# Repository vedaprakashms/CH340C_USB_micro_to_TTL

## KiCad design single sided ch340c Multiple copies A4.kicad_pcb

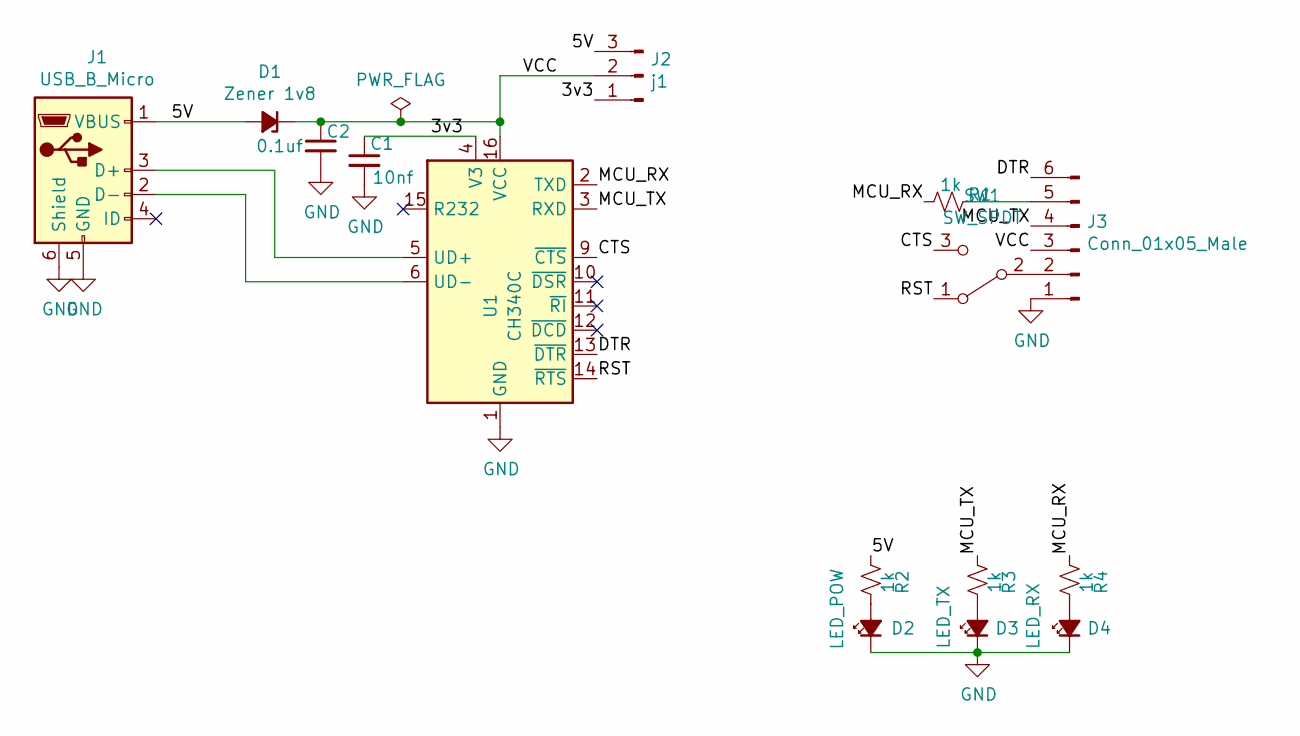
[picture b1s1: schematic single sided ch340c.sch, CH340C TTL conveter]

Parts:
C1: 10nf; C_0805_2012Metric_Pad1.15x1.40mm_HandSolder
C2: 0.1uf; C_0805_2012Metric_Pad1.15x1.40mm_HandSolder
D1: Zener 1v8; D_0805_2012Metric_Pad1.15x1.40mm_HandSolder
D2: LED_POW; LED_0805_2012Metric_Pad1.15x1.40mm_HandSolder
D3: LED_TX; LED_0805_2012Metric_Pad1.15x1.40mm_HandSolder
D4: LED_RX; LED_0805_2012Metric_Pad1.15x1.40mm_HandSolder
J1: USB_B_Micro; USB_Micro-B_Molex_47346-0001
J2: j1; PinHeader_1x03_P2.54mm_Vertical
J3: Conn_01x05_Male; PinHeader_1x06_P2.54mm_Vertical
R1, R2, R3, R4: 1k; R_0805_2012Metric_Pad1.15x1.40mm_HandSolder
SW1: SW_SPDT; PinHeader_1x03_P2.54mm_Vertical
U1: CH340C; SOIC-16_3.9x9.9mm_P1.27mm

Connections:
/3v3: C1.1, J2.1, U1.4 (V3)
/5V: D1.2 (A), J1.1 (VBUS), J2.3, R2.1
/CTS: SW1.3 (C), U1.9 (~CTS)
/DTR: J3.6, U1.13 (~DTR)
/MCU_RX: R1.1, R4.1, U1.2 (TXD)
/MCU_TX: J3.4, R3.1, U1.3 (RXD)
/RST: SW1.1 (A), U1.14 (~RTS)
/VCC: C2.1, D1.1 (K), J2.2, J3.3, U1.16 (VCC)
GND: C1.2, C2.2, D2.1 (K), D3.1 (K), D4.1 (K), J1.5 (GND), J1.6 (Shield), J3.1, U1.1 (GND)
unnamed: D2.2 (A), R2.2
unnamed: D3.2 (A), R3.2
unnamed: D4.2 (A), R4.2
unnamed: J1.2 (D-), U1.6 (UD-)
unnamed: J1.3 (D+), U1.5 (UD+)
unnamed: J3.2, SW1.2 (B)
unnamed: J3.5, R1.2

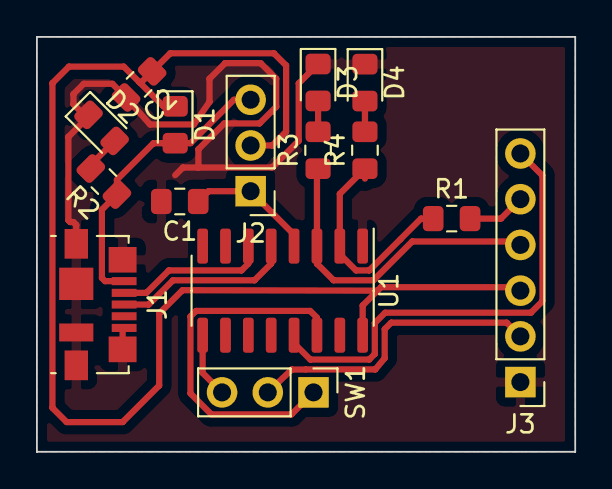
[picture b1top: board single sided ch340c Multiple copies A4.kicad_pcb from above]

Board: 2 copper layers, 29.9 x 23.1 mm, 15 parts (0 on the bottom side), 16 nets.

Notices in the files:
single sided ch340c.sch:
MIT licensed
